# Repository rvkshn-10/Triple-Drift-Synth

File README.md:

# Triple Drift Synth

Triple Drift is a small, standalone drone synthesizer designed for Hack Club’s Week 3 music challenge: circuits that turn voltage into sound. It combines three independently adjustable voices inside a custom 3D-printed enclosure.

## How it works

Each voice is a 555 timer circuit that outputs a repeating electrical signal. You hear a different note because the frequency of the oscillation is changed by the pitch knob. Each voice also has a level control and mute switch.

The three signals feed a mixer, master volume control and amplifier that drives a built-in speaker. The voices are closely tuned together. This creates slow beating and pulsing sounds. There is also a momentary PLAY button and a continuous DRONE mode to the instrument.

## Why I made it

I wanted to see how basic electronic components could make an instrument without a computer or pre-recorded sounds. This project is a combination of circuit design, PCB layout and mechanical CAD with a goal of a total budget of $65 including fabrication and shipping.

## Design

The PCB was designed in KiCad, the enclosure was designed in Autodesk Fusion. The enclosure has labeled controls, PCB mounting posts, a battery cradle, internal wire clips and a speaker grille.

## Current status

PCB and enclosure design is finished. The enclosure has been checked for digital interference and the exported print meshes have been checked. Physical assembly, sound testing and final hardware fit are still to come. The full $65 budget has not yet been confirmed.

This is an analog instrument, so it does not require firmware.

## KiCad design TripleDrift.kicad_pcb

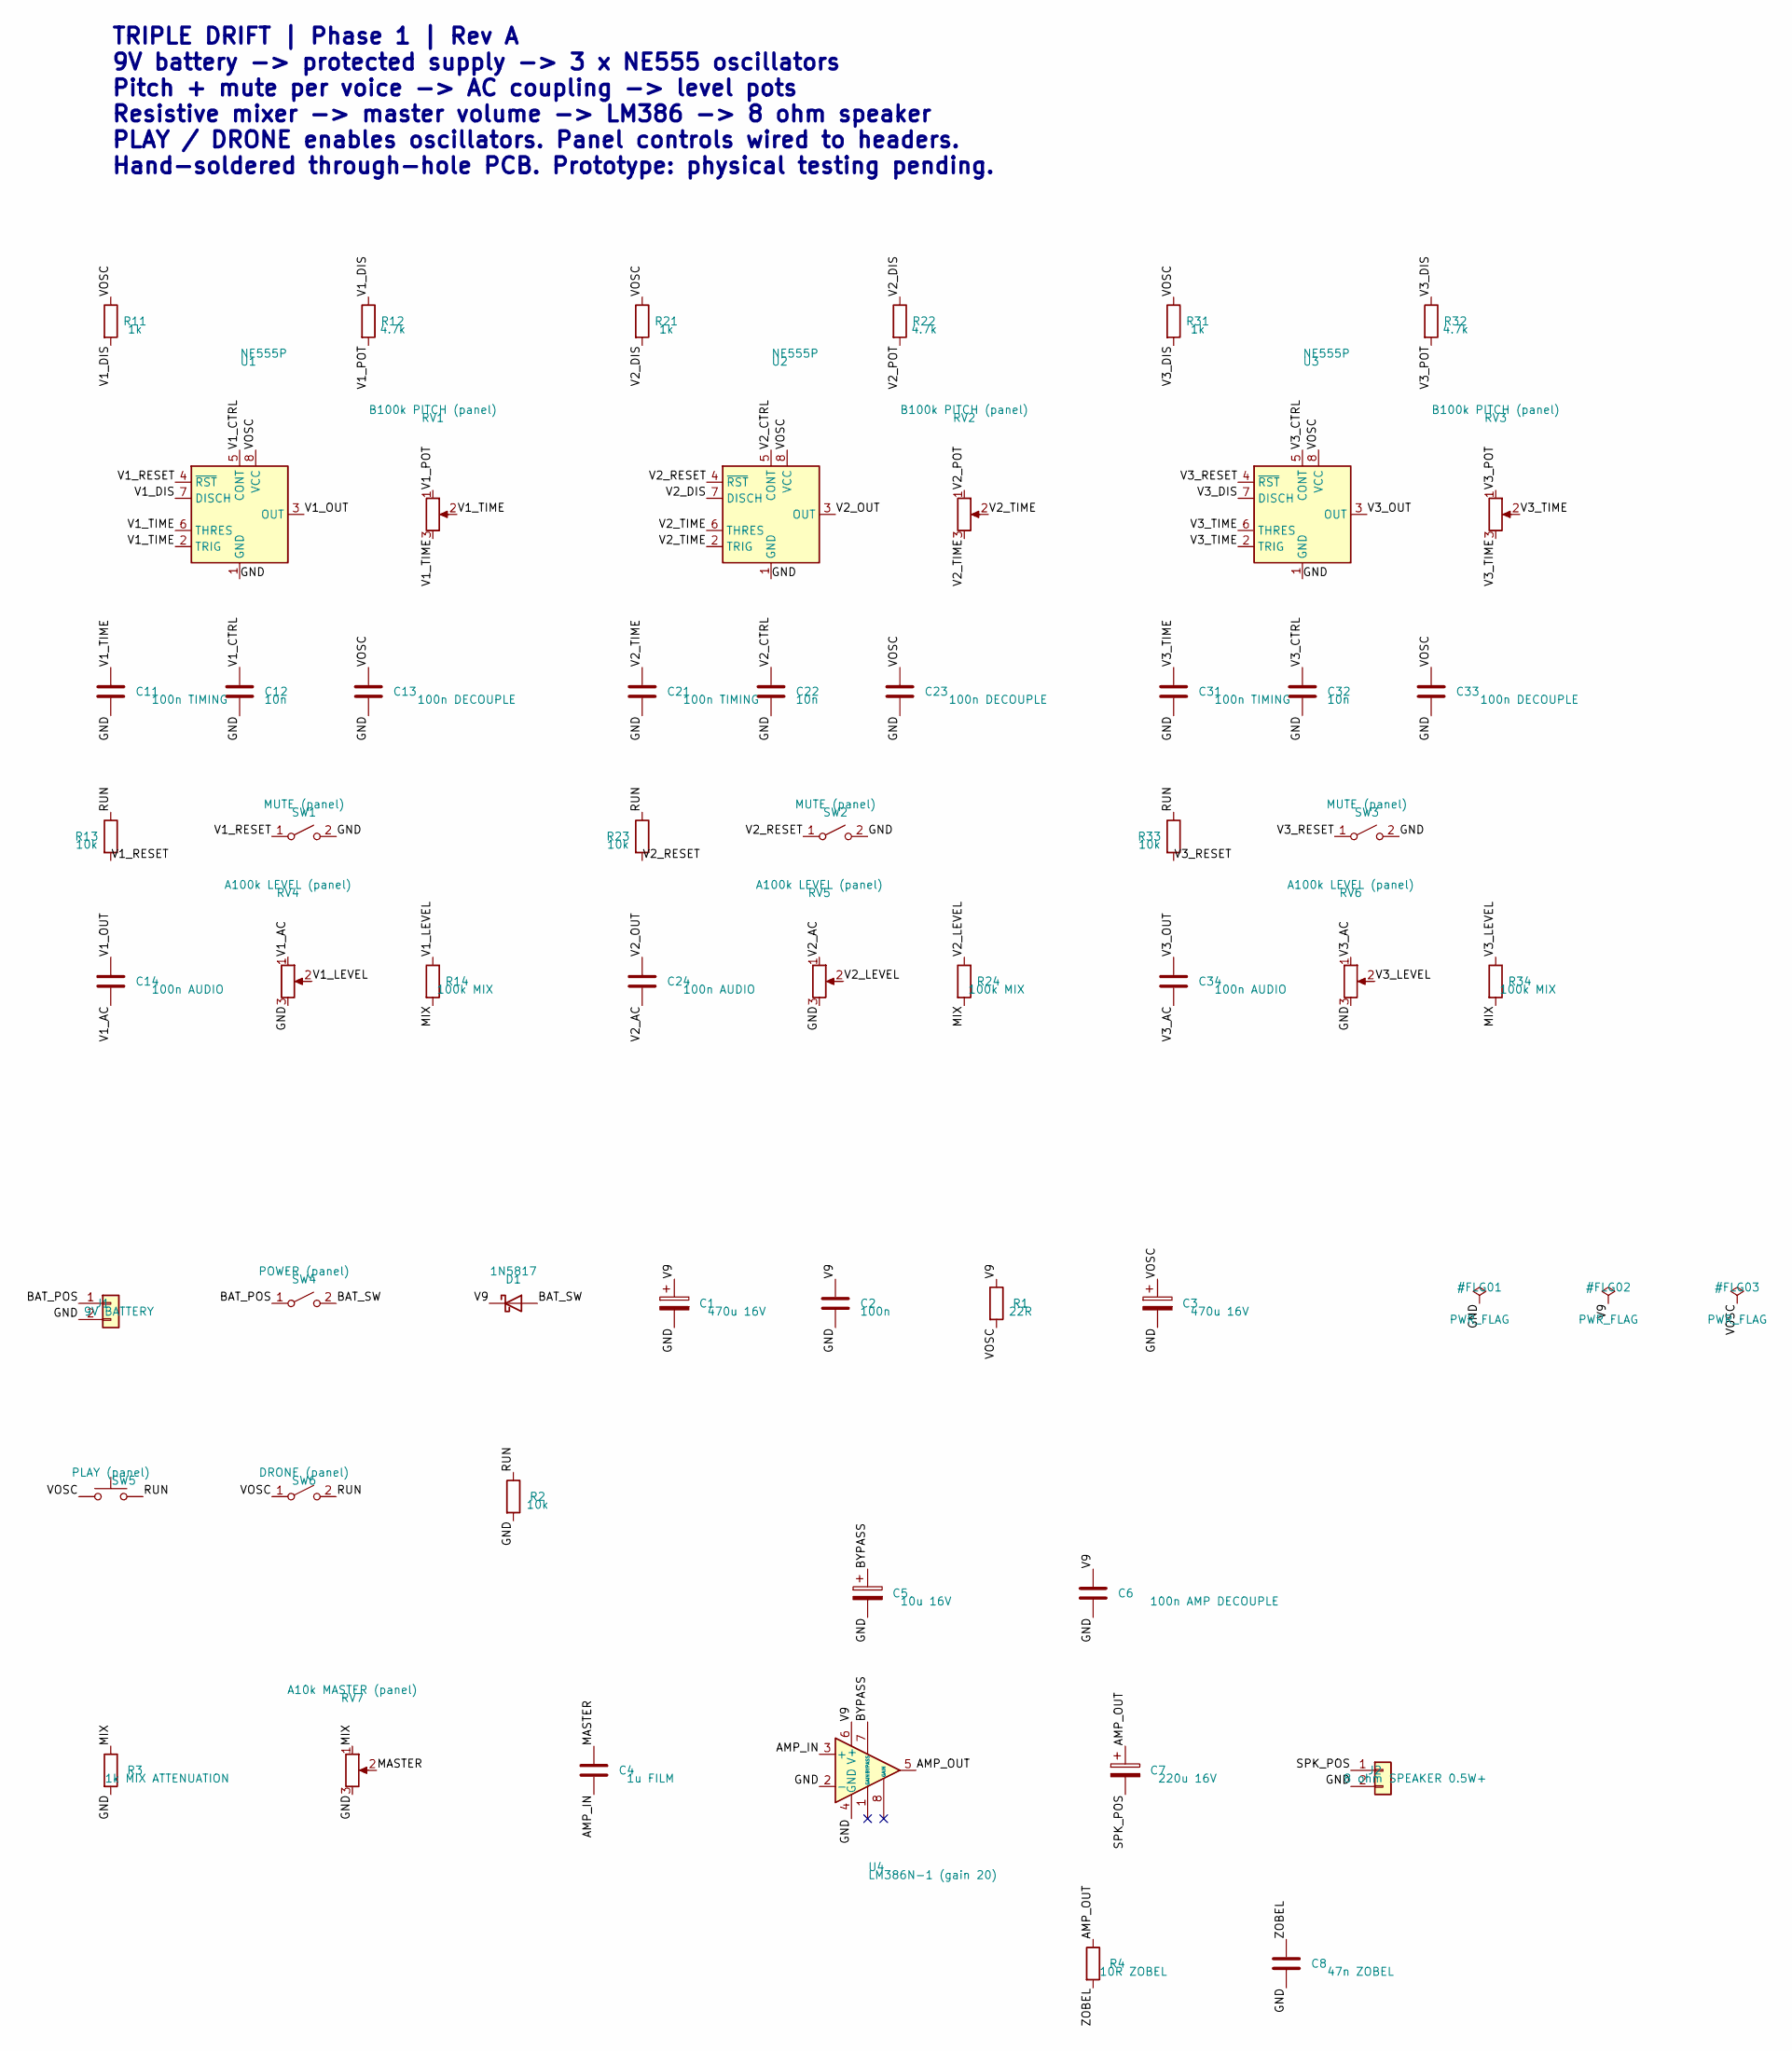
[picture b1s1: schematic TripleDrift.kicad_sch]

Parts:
C1, C3: 470u 16V; CP_Radial_D8.0mm_P3.50mm
C2: 100n; C_Disc_D5.0mm_W2.5mm_P5.00mm
C4: 1u FILM; C_Rect_L7.2mm_W2.5mm_P5.00mm
C5: 10u 16V; CP_Radial_D5.0mm_P2.00mm
C6: 100n AMP DECOUPLE; C_Disc_D5.0mm_W2.5mm_P5.00mm
C7: 220u 16V; CP_Radial_D8.0mm_P3.50mm
C8: 47n ZOBEL; C_Disc_D5.0mm_W2.5mm_P5.00mm
C11, C21, C31: 100n TIMING; C_Disc_D5.0mm_W2.5mm_P5.00mm
C12, C22, C32: 10n; C_Disc_D5.0mm_W2.5mm_P5.00mm
C13, C23, C33: 100n DECOUPLE; C_Disc_D5.0mm_W2.5mm_P5.00mm
C14, C24, C34: 100n AUDIO; C_Disc_D5.0mm_W2.5mm_P5.00mm
D1: 1N5817; D_DO-41_SOD81_P10.16mm_Horizontal
J1: 9V BATTERY; PinHeader_1x02_P2.54mm_Vertical
J2: 8 ohm SPEAKER 0.5W+; PinHeader_1x02_P2.54mm_Vertical
R1: 22R; R_Axial_DIN0207_L6.3mm_D2.5mm_P10.16mm_Horizontal
R2, R13, R23, R33: 10k; R_Axial_DIN0207_L6.3mm_D2.5mm_P10.16mm_Horizontal
R3: 1k MIX ATTENUATION; R_Axial_DIN0207_L6.3mm_D2.5mm_P10.16mm_Horizontal
R4: 10R ZOBEL; R_Axial_DIN0207_L6.3mm_D2.5mm_P10.16mm_Horizontal
R11, R21, R31: 1k; R_Axial_DIN0207_L6.3mm_D2.5mm_P10.16mm_Horizontal
R12, R22, R32: 4.7k; R_Axial_DIN0207_L6.3mm_D2.5mm_P10.16mm_Horizontal
R14, R24, R34: 100k MIX; R_Axial_DIN0207_L6.3mm_D2.5mm_P10.16mm_Horizontal
RV1, RV2, RV3: B100k PITCH (panel); PinHeader_1x03_P2.54mm_Vertical
RV4, RV5, RV6: A100k LEVEL (panel); PinHeader_1x03_P2.54mm_Vertical
RV7: A10k MASTER (panel); PinHeader_1x03_P2.54mm_Vertical
SW1, SW2, SW3: MUTE (panel); PinHeader_1x02_P2.54mm_Vertical
SW4: POWER (panel); PinHeader_1x02_P2.54mm_Vertical
SW5: PLAY (panel); PinHeader_1x02_P2.54mm_Vertical
SW6: DRONE (panel); PinHeader_1x02_P2.54mm_Vertical
U1, U2, U3: NE555P; DIP-8_W7.62mm
U4: LM386N-1 (gain 20); DIP-8_W7.62mm

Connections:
/AMP_IN: C4.2, U4.3 (+)
/AMP_OUT: C7.1, R4.1, U4.5
/BAT_POS: J1.1, SW4.1 (A)
/BAT_SW: D1.2 (A), SW4.2 (B)
/BYPASS: C5.1, U4.7 (BYPASS)
/GND: C1.2, C2.2, C3.2, C5.2, C6.2, C8.2, C11.2, C12.2, C13.2, C21.2, C22.2, C23.2, C31.2, C32.2, C33.2, J1.2, J2.2, R2.2, R3.2, RV4.3, RV5.3, RV6.3, RV7.3, SW1.2 (B), SW2.2 (B), SW3.2 (B), U1.1 (GND), U2.1 (GND), U3.1 (GND), U4.2 (-), U4.4 (GND)
/MASTER: C4.1, RV7.2
/MIX: R3.1, R14.2, R24.2, R34.2, RV7.1
/RUN: R2.1, R13.1, R23.1, R33.1, SW5.2, SW6.2 (B)
/SPK_POS: C7.2, J2.1
/V1_AC: C14.2, RV4.1
/V1_CTRL: C12.1, U1.5 (CONT)
/V1_DIS: R11.2, R12.1, U1.7 (DISCH)
/V1_LEVEL: R14.1, RV4.2
/V1_OUT: C14.1, U1.3 (OUT)
/V1_POT: R12.2, RV1.1
/V1_RESET: R13.2, SW1.1 (A), U1.4 (~RST)
/V1_TIME: C11.1, RV1.2, RV1.3, U1.2 (TRIG), U1.6 (THRES)
/V2_AC: C24.2, RV5.1
/V2_CTRL: C22.1, U2.5 (CONT)
/V2_DIS: R21.2, R22.1, U2.7 (DISCH)
/V2_LEVEL: R24.1, RV5.2
/V2_OUT: C24.1, U2.3 (OUT)
/V2_POT: R22.2, RV2.1
/V2_RESET: R23.2, SW2.1 (A), U2.4 (~RST)
/V2_TIME: C21.1, RV2.2, RV2.3, U2.2 (TRIG), U2.6 (THRES)
/V3_AC: C34.2, RV6.1
/V3_CTRL: C32.1, U3.5 (CONT)
/V3_DIS: R31.2, R32.1, U3.7 (DISCH)
/V3_LEVEL: R34.1, RV6.2
/V3_OUT: C34.1, U3.3 (OUT)
/V3_POT: R32.2, RV3.1
/V3_RESET: R33.2, SW3.1 (A), U3.4 (~RST)
/V3_TIME: C31.1, RV3.2, RV3.3, U3.2 (TRIG), U3.6 (THRES)
/V9: C1.1, C2.1, C6.1, D1.1 (K), R1.1, U4.6 (V+)
/VOSC: C3.1, C13.1, C23.1, C33.1, R1.2, R11.1, R21.1, R31.1, SW5.1, SW6.1 (A), U1.8 (VCC), U2.8 (VCC), U3.8 (VCC)
/ZOBEL: C8.1, R4.2

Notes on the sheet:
TRIPLE DRIFT | Phase 1 | Rev A 9V battery -> protected supply -> 3 x NE555 oscillators Pitch + mute per voice -> AC coupling -> level pots Resistive mixer -> master volume -> LM386 -> 8 ohm speaker PLAY / DRONE enables oscillators. Panel controls wired to headers. Hand-soldered through-hole PCB. Pr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

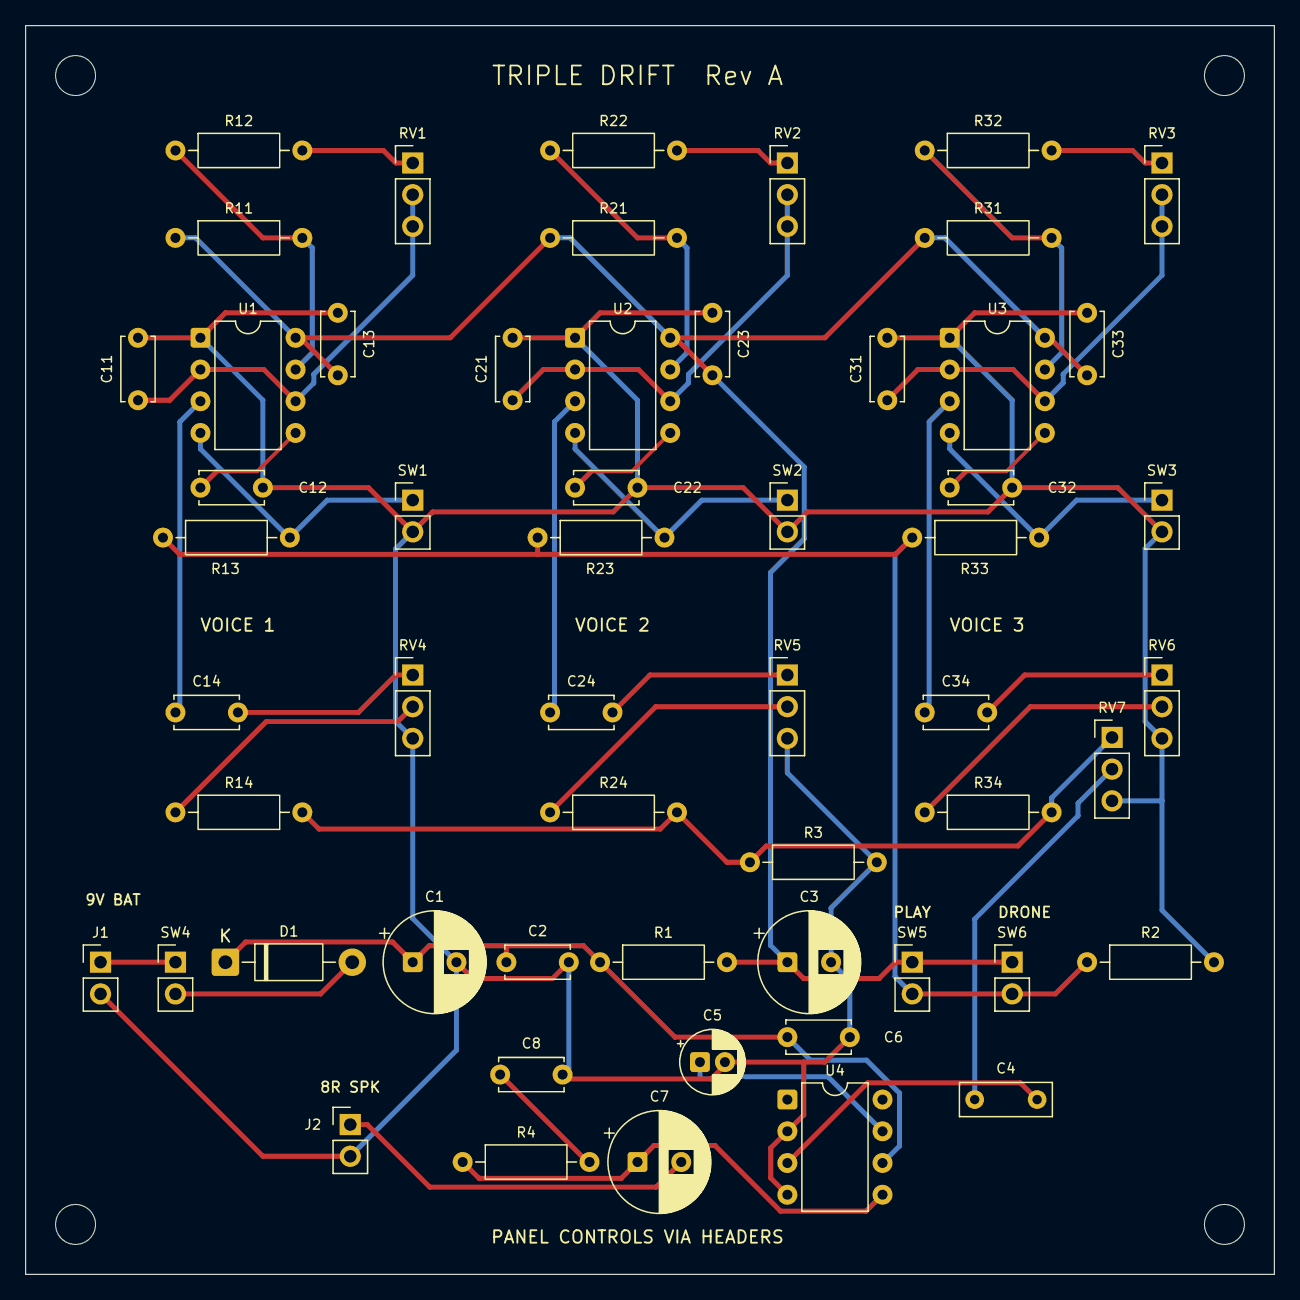
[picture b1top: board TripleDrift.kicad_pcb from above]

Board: 2 copper layers, 100.0 x 100.0 mm, 60 parts (0 on the bottom side), 37 nets.

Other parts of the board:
MH1, MH2, MH3, MH4: MountingHole_3.2mm_M3

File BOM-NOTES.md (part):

# Triple Drift purchasing draft

Updated October 24, 2026. Currency: USD. **The revised estimate is $85.41, down $15.96 from $101.37, but still $20.41 over the $65 limit. This is not a verified delivered quote.** It assumes enough matching screws and nuts remain in the existing M3 kit. The revised CAD still requires a new printing quote.

`BOM.csv` keeps Part, Qty, Unit, Total, Vendor and Link. Unit means cost per purchased unit in USD. Full purchase quantities are charged. Resistors and ceramic capacitors are budgeted in ten-piece purchases. Reused parts have zero new purchase cost and stay visible in the list.

## Changes selected by total cost

- The speaker is now Tayda A-4117 / HY57MS0810-H8.4, 57 mm, 8 ohms, 1 W, listed at $0.95. It replaces the $4.46 Mouser speaker, $8 separate shipping allowance and $0.45 speaker tariff reserve. The existing $8 Tayda shipping/import allowance remains unverified and must cover the revised order.
- Keep six 100 nF film capacitors for C11/C21/C31 timing and C14/C24/C34 audio coupling. Replace C2/C6/C13/C23/C33 bypass capacitors with 100 nF ceramic capacitors. Buy ten at the listed $0.01 each and use five. The three 10 nF control-pin bypass capacitors C12/C22/C32 also become ceramics, bought as ten at $0.01 each. These changes save $0.50 after rounding full line purchases. Supplier category lists 3 mm lead spacing; carefully form the leads for the PCB's 5 mm holes without stressing the ceramic body. Electrical values and voltage ratings remain suitable for the 9 V circuit. No schematic or PCB edits were made.
- Reuse ten matching M3 mounting screws: four M3x8 for the lid and six M3x6 for PCB/bridge. Reuse seven M3x8 headed screws and seven M3 nuts for the revised knobs. This removes the former $4 hardware purchase allowance. Check actual leftover counts, head dimensions and nut thickness before printing. The prior keyboard BOM identifies a nylon fastener kit, so metal set screws are no longer assumed to be included.
- Add $0.50 as an unquoted purchase allowance for thin compliant speaker-pad material. This is not a confirmed retail pack price.

Amazon Prime was considered. The checked 40 mm speaker two-pack was $5.99 with advertised free Prime delivery, and the 555/LM386 IC assortment was $8.10. The selected speaker and ICs from Tayda total $2.55 before shipping, compared with $14.09 for those two Amazon packs. Since other components still require the Tayda order, switching just these parts to Amazon adds $11.54 in merchandise cost without eliminating that shipment. No separate Prime subscription cost is charged because the user already has Prime. Other unselected Amazon packs are not represented as verified cheapest options.

## CAD status

A separate **Triple Drift - Cost revision - 57mm speaker** document was created in **Admin Project**. The original completed Phase 3 design was preserved. The revision adds the larger speaker locator/diagonal bridge/grille, repositions the voice controls and legends, widens pot holes to 7.7 mm and adjusts knob height for 15 mm pot shafts. The selected DS-227 PLAY switch uses a 12.7 mm clearance opening and is raised to avoid the PCB. The knobs now use captive M3 nuts instead of tapped resin set-screw holes.

The completed 461-entry revision is saved in Admin Project and passed the 115-body digital interference check with no printed-part collisions. Its native F3D archive was reopened in Fusion with the final M3 nut-channel knob features present and no feature errors or warnings. Updated F3D, STEP, five STL files and verification reports are in cad/cost-revision. All STL meshes passed closed-edge, positive-volume and flat-bed checks. Physical fit, wiring, resin durability, sound and assembly have not been tested. No parts have been ordered.

## Fabrication and delivered-cost assumptions

All five plastic part types remain included: base x1, lid x1, knobs x7, retaining bridge x1 and battery pull grip x1. The printing line values are **prior-geometry price allowances**, not quotes for the revised files. The former quote was $18.16 for 9600 white resin. Its country-level print shipping estimate was $14.03. New model upload, supplier review and address-level checkout are still required.

PCB fabrication is a $2 base-price allowance for a five-board batch of 100 x 100 mm, two-layer, 1.6 mm boards. It is not an uploaded Gerber quote. The $8 separate PCB shipping allowance remains until an actual quote replaces it. JLC supports combined payment, but shared shipping or a shipping saving has not been established.

The $8 Tayda shipping/import allowance, $7 sales/use-tax reserve and hardware/consumable allowances are unquoted estimates and may be insufficient. The JLC resin reserve of $7.26 and PCB reserve of $0.70 follow its published 40% plastic/35% PCB policy using the old printing allowance and PCB base price. Replace reserves with actual charges and avoid counting duties twice when checkout already includes them. No import charges are assumed waived because an order is small.

Self-soldering is assumed. Wire is soldered directly to PCB connector pads, avoiding headers and mating plugs. Wire/heat-shrink, battery, solder, feet/ribbon/ties remain purchase allowances because leftover quantities were not confirmed. Soldering iron, cutters and meter are assumed borrowed. Purchasing tools or assembly services would increase the total.

## Remaining fit checks

The capacitor body clearances, especially the 1 uF film part, still need checking against PCB footprints. Pot mounting hardware and all shaft/bushing tolerances need physical verification. The speaker drawing informed its CAD envelope, but terminal position, the soft pad and wiring bends require an actual fit test. The existing M3 kit must contain suitable leftover screws and nuts; the zero-cost reuse rows are conditional on that stock.

## Sources

- [Speaker and $0.95 price](https://www.taydaelectronics.com/hardware-tools/speakers/myl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
- [Speaker supplier drawing](https://www.taydaelectronics.com/datasheets/files/HY57MS0810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
- [Ceramic capacitor prices](https://www.taydaelectronics.com/capacitors/ceramic-disc-cap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
- [Pitch pot dimensions](https://www.taydaelectronics.com/datasheets/files/A-5606.pdf)
- [Toggle dimensions](https://www.taydaelectronics.com/datasheets/files/A-4567.pdf)
- [PLAY button dimensions](https://www.taydaelectronics.com/datasheets/files/A-6454.pdf)
- [Amazon speaker comparison](https://www.amazon.com/dp/B0GR43H68T)
- [Amazon IC assortment comparison](https://www.amazon.com/dp/B08JTM2SMJ)
- [JLC US tariff policy](https://jlc3dp.com/help/article/us-tariff-policy-faq)
- [JLC combined-order payment instructions](https://jlc3dp.com/help/article/how-to-combine-orders-for-jl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
- [California sales and use tax rates](https://www.cdtfa.ca.gov/taxes-and-fees/rates.htm)

## Unchanged part details


- **NE555P DIP-8 timer** — Listed price. References: U1 U2 U3. A-249
- **LM386N-1 DIP-8 amplifier** — Listed price. References: U4. A-994; amplifier is on PCB; no extra module
- **1N5817 Schottky diode** — Listed price. References: D1. A-159
- **22 ohm 1/4W resistor** — Listed price. References: R1. Buy 10; use 1; full purchase quantity charged
- **10 ohm 1/4W resistor** — Listed price. References: R4. Buy 10; use 1; full purchase quantity charged
- **1k ohm 1/4W resistor** — Listed price. References: R3 R11 R21 R31. Buy 10; use 4; full purchase quantity charged
- **4.7k ohm 1/4W resistor** — Listed price. References: R12 R22 R32. Buy 10; use 3; full purchase quantity charged
- **10k ohm 1/4W resistor** — Listed price. References: R2 R13 R23 R33. Buy 10; use 4; full purchase quantity charged
- **100k ohm 1/4W resistor** — Listed price. References: R14 R24 R34. Buy 10; use 3; full purchase quantity charged
- **470uF 16V radial capacitor** — Listed price. References: C1 C3. A-4521; 8mm diameter; 3.5mm pitch
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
